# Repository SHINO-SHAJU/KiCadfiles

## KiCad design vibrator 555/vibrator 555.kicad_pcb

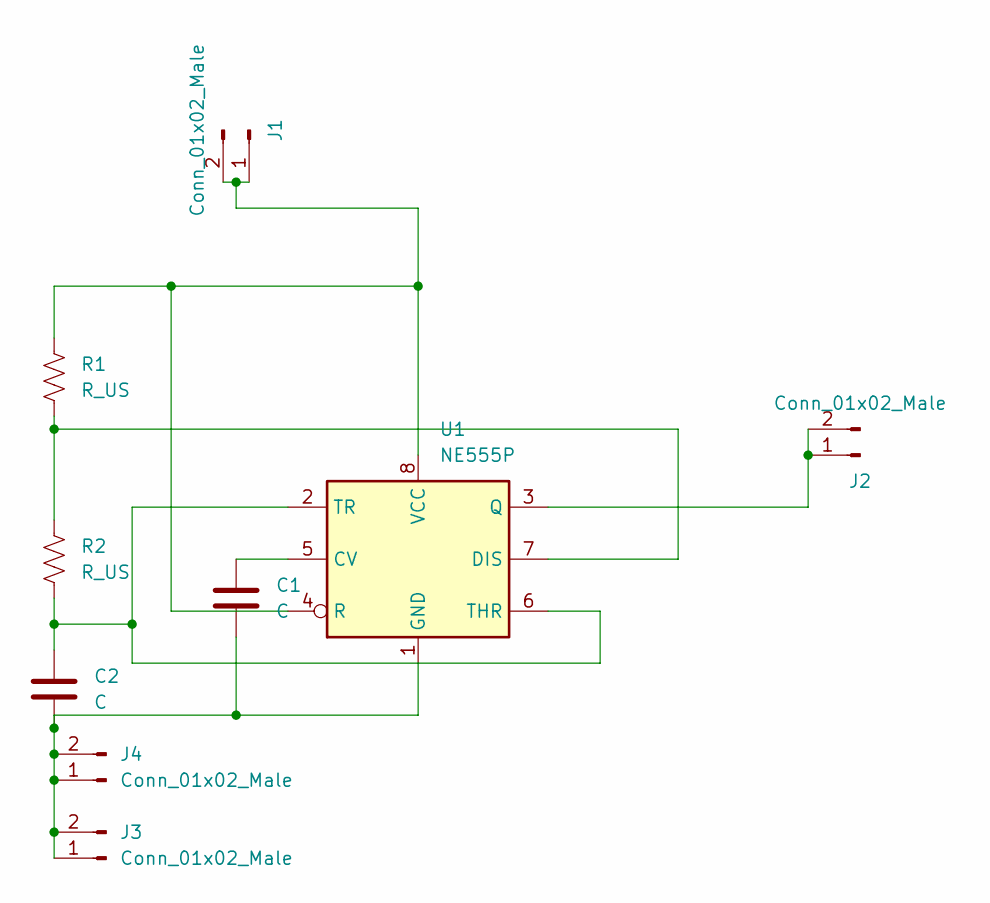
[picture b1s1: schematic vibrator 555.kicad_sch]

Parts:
C1: C; C_Disc_D4.3mm_W1.9mm_P5.00mm
C2: C; CP_Radial_D10.0mm_P5.00mm
J1, J2, J3, J4: Conn_01x02_Male; PinHeader_1x02_P2.54mm_Vertical
R1, R2: R_US; R_Axial_DIN0414_L11.9mm_D4.5mm_P15.24mm_Horizontal
U1: NE555P; DIP-8_W7.62mm

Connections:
unnamed: C1.1, U1.5 (CV)
unnamed: C1.2, C2.2, J3.1, J3.2, J4.1, J4.2, U1.1 (GND)
unnamed: C2.1, R2.2, U1.2 (TR), U1.6 (THR)
unnamed: J1.1, J1.2, R1.1, U1.4 (R), U1.8 (VCC)
unnamed: J2.1, J2.2, U1.3 (Q)
unnamed: R1.2, R2.1, U1.7 (DIS)

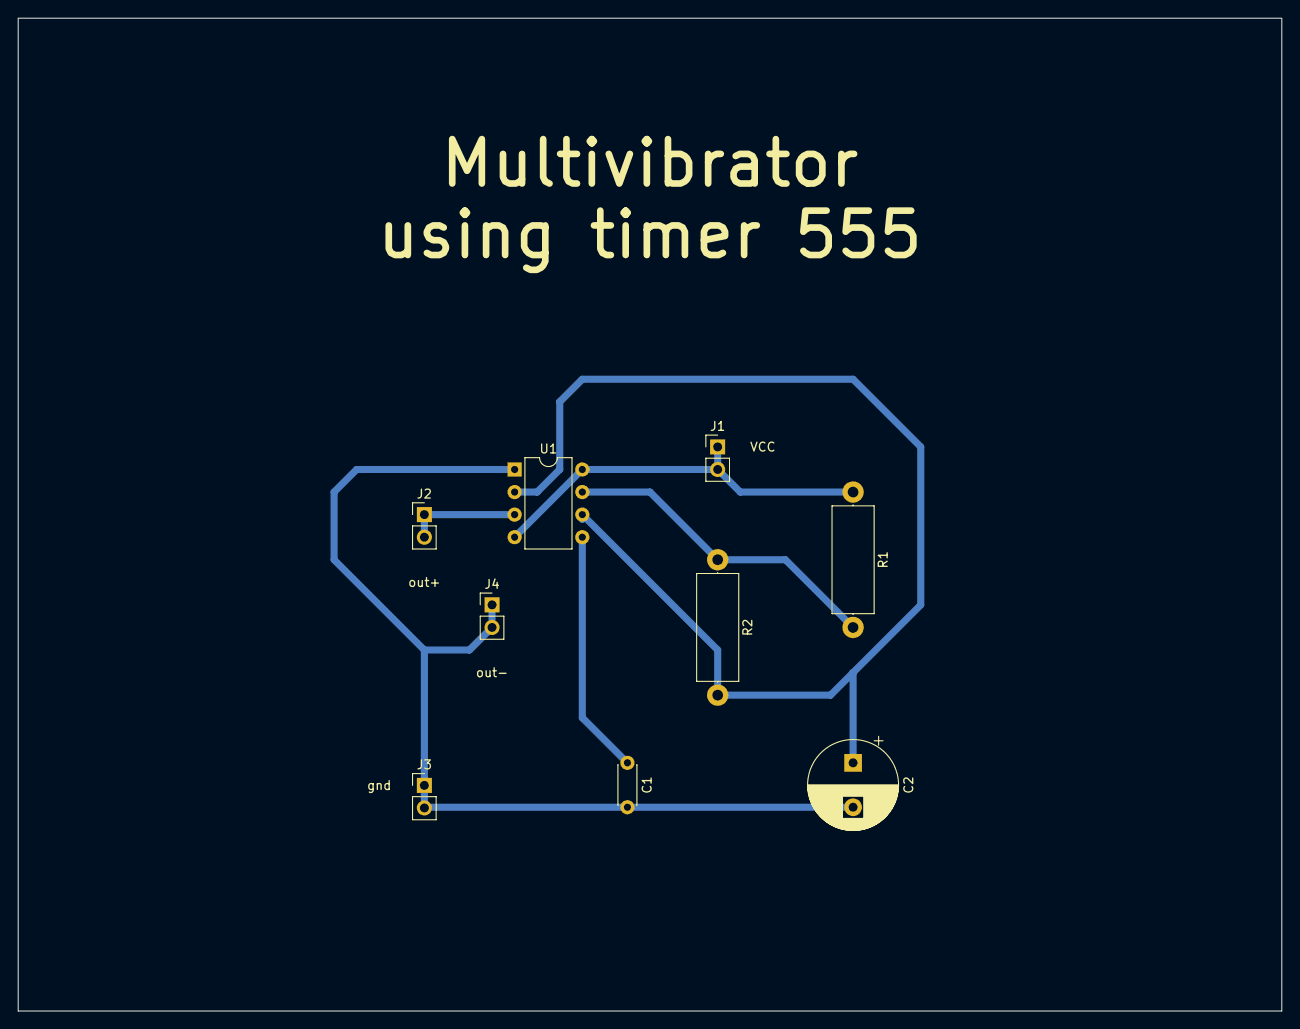
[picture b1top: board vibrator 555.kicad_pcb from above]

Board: 2 copper layers, 142.2 x 111.8 mm, 9 parts (0 on the bottom side), 6 nets.

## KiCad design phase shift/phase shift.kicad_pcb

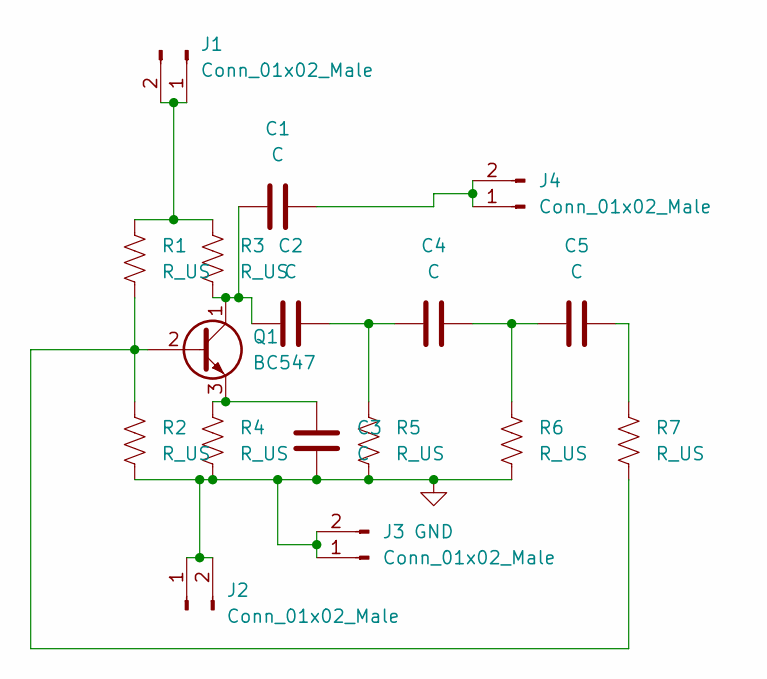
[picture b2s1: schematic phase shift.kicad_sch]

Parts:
C1, C2, C4, C5: C; C_Disc_D7.0mm_W2.5mm_P5.00mm
C3: C; CP_Radial_D10.0mm_P5.00mm
J1, J2, J3, J4: Conn_01x02_Male; PinHeader_1x02_P2.54mm_Vertical
Q1: BC547; TO-92L_Wide
R1, R2, R3, R4, R5, R6, R7: R_US; R_Axial_DIN0414_L11.9mm_D4.5mm_P20.32mm_Horizontal

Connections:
GND: C3.2, J2.1, J2.2, J3.1, J3.2, R2.1, R4.2, R5.2, R6.1
unnamed: C1.1, C2.1, Q1.1 (C), R3.2
unnamed: C1.2, J4.1, J4.2
unnamed: C2.2, C4.1, R5.1
unnamed: C3.1, Q1.3 (E), R4.1
unnamed: C4.2, C5.1, R6.2
unnamed: C5.2, R7.2
unnamed: J1.1, J1.2, R1.1, R3.1
unnamed: Q1.2 (B), R1.2, R2.2, R7.1

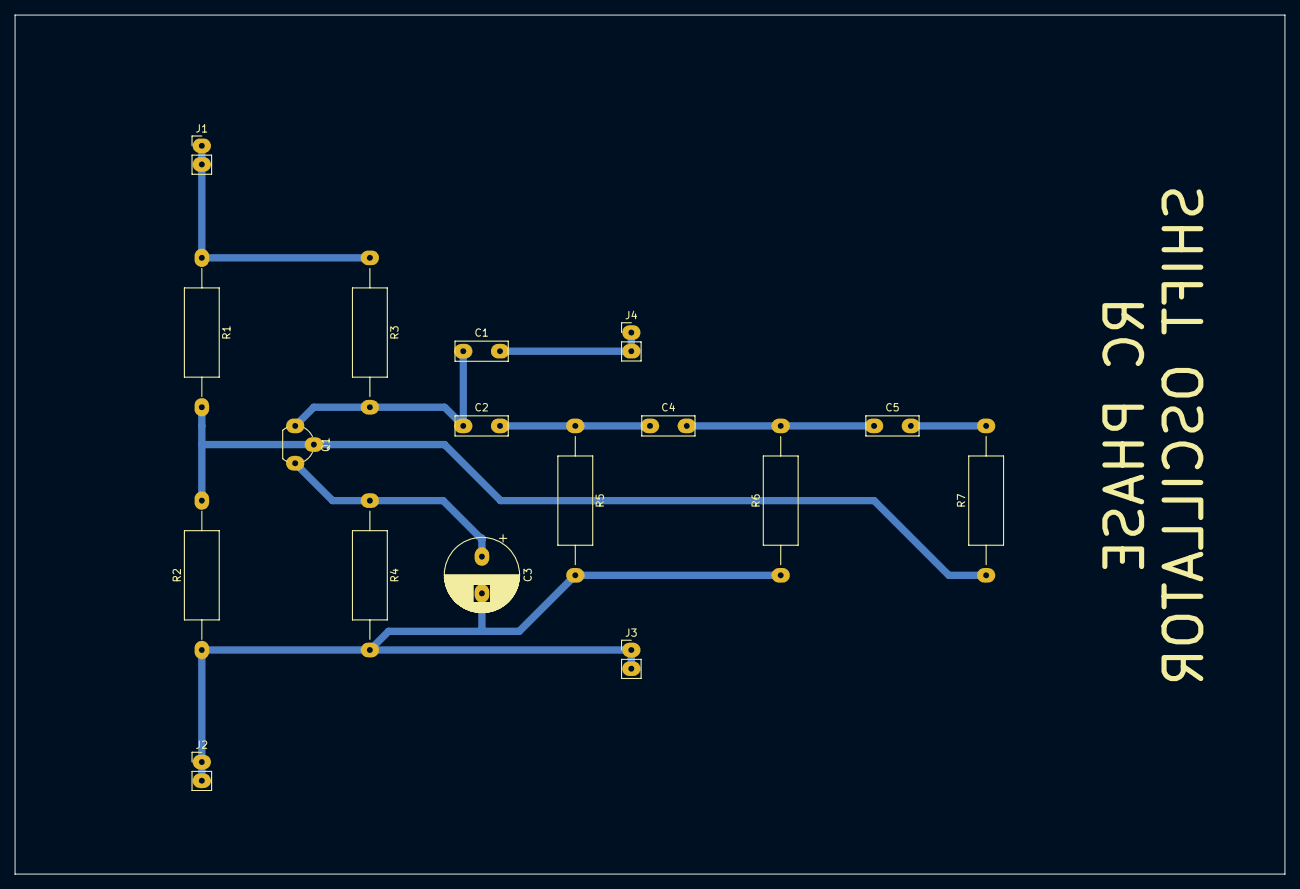
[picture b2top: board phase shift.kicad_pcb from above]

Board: 2 copper layers, 172.7 x 116.8 mm, 17 parts (0 on the bottom side), 9 nets.

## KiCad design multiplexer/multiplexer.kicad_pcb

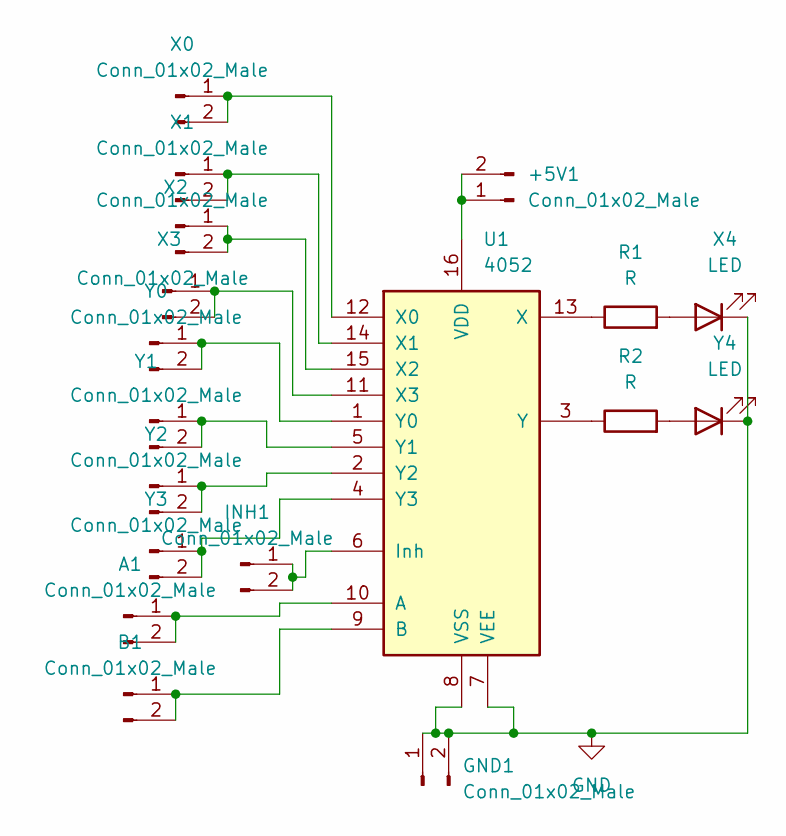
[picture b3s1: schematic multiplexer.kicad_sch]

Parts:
+5V1: Conn_01x02_Male; PinHeader_1x02_P2.54mm_Vertical
A1: Conn_01x02_Male; PinHeader_1x02_P2.54mm_Vertical
B1: Conn_01x02_Male; PinHeader_1x02_P2.54mm_Vertical
GND1: Conn_01x02_Male; PinHeader_1x02_P2.54mm_Vertical
INH1: Conn_01x02_Male; PinHeader_1x02_P2.54mm_Vertical
R1, R2: R; R_Axial_DIN0207_L6.3mm_D2.5mm_P10.16mm_Horizontal
U1: 4052; DIP-16_W7.62mm
X0, X1, X2, X3: Conn_01x02_Male; PinHeader_1x02_P2.54mm_Vertical
X4: LED; LED_D5.0mm
Y0, Y1, Y2, Y3: Conn_01x02_Male; PinHeader_1x02_P2.54mm_Vertical
Y4: LED; LED_D5.0mm

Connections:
GND: GND1.1, GND1.2, U1.7 (VEE), U1.8 (VSS), X4.1 (K), Y4.1 (K)
unnamed: +5V1.1, +5V1.2, U1.16 (VDD)
unnamed: A1.1, A1.2, U1.10 (A)
unnamed: B1.1, B1.2, U1.9 (B)
unnamed: INH1.1, INH1.2, U1.6 (Inh)
unnamed: R1.1, U1.13 (X)
unnamed: R1.2, X4.2 (A)
unnamed: R2.1, U1.3 (Y)
unnamed: R2.2, Y4.2 (A)
unnamed: U1.1 (Y0), Y0.1, Y0.2
unnamed: U1.2 (Y2), Y2.1, Y2.2
unnamed: U1.4 (Y3), Y3.1, Y3.2
unnamed: U1.5 (Y1), Y1.1, Y1.2
unnamed: U1.11 (X3), X3.1, X3.2
unnamed: U1.12 (X0), X0.1, X0.2
unnamed: U1.14 (X1), X1.1, X1.2
unnamed: U1.15 (X2), X2.1, X2.2

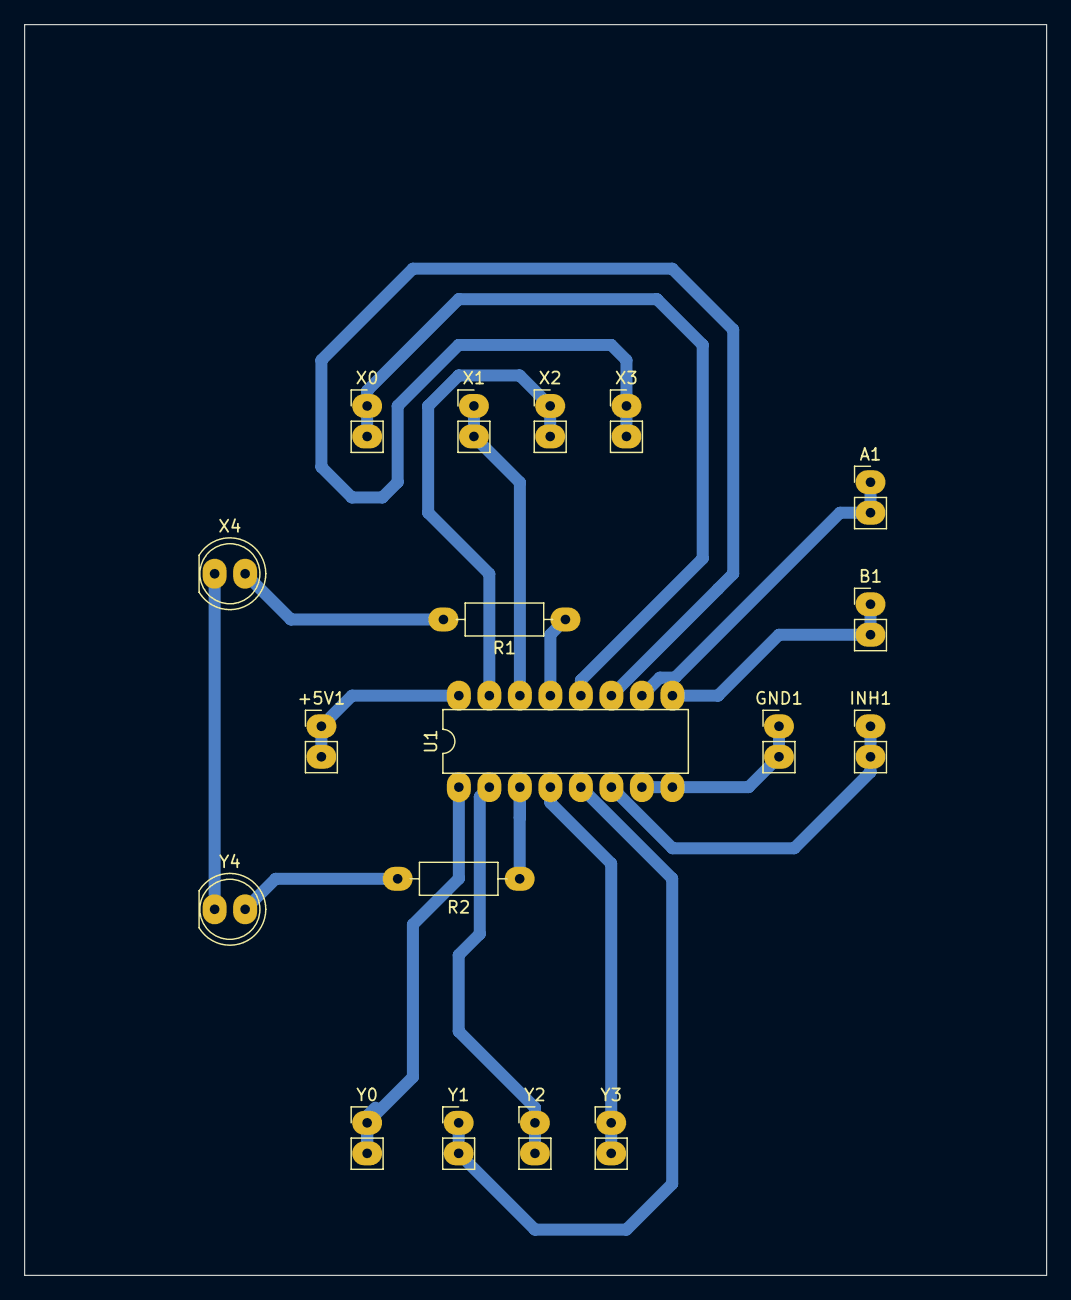
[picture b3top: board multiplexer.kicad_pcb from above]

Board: 2 copper layers, 85.1 x 104.1 mm, 18 parts (0 on the bottom side), 17 nets.
